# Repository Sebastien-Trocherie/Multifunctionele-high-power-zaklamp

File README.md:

# Multifunctionele-high-power-zaklamp

Het doel van dit project is om een zaklamp te maken die ik in verschillende situaties kan gebruiken, 

De zaklamp moet dus zeker 200-300m ver schijnen, om dit bereik te realiseren heeft de lamp toch een lichtintensiteit van meer dan 1000 lumen nodig. De bedoeling is dan ook om een high power LED te vinden die deze lichtintensiteit kan leveren. Verder moet de zaklamp zeker niet altijd zo fel zijn dus zal deze via PWM dimbaar zijn. Als extra functionaliteit wil ik via Bluetooth een string sturen naar de microcontroller die deze zal omzetten in morse code.

Het project bestaat uit 3 hoofddelen.

1) De Li-Ion batterij lader.

2) De LED driver die de LED zal aandrijven.

3) De microcontroller die het PWM signaal zal genereren en de morse code zal genereren.

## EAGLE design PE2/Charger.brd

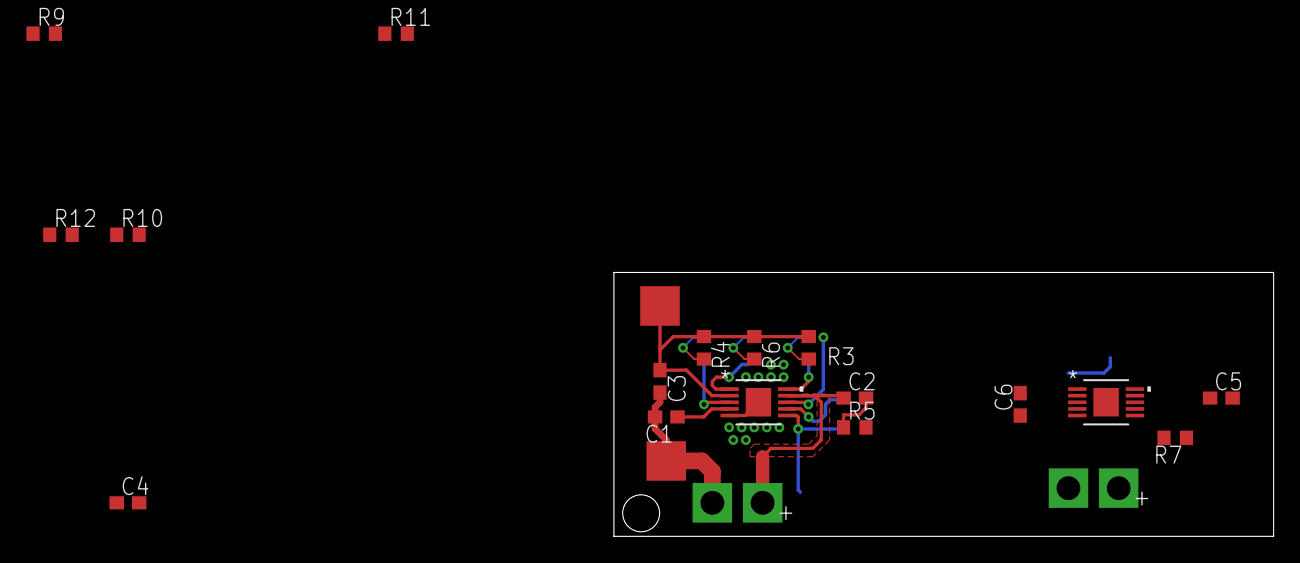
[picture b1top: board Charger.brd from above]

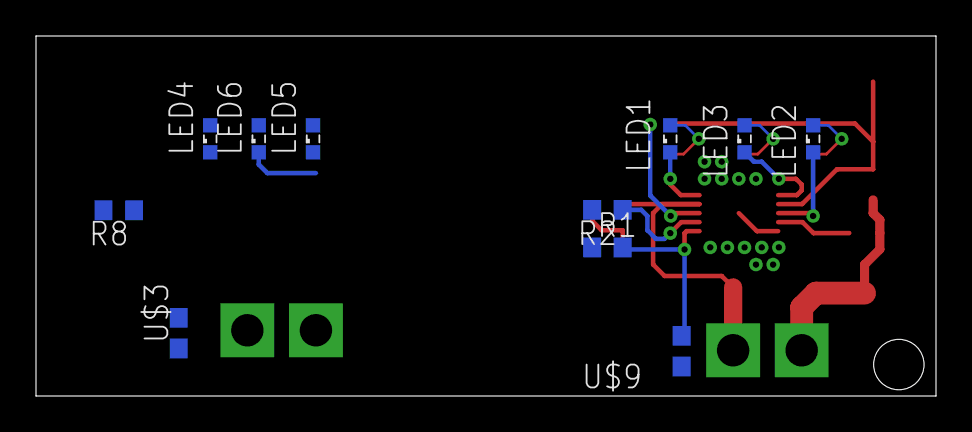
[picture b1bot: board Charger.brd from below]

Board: 2 copper layers, 50.0 x 20.0 mm, 32 parts (11 on the bottom side), 26 nets.

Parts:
BAT1: BATBAT; BAT2
BAT2: BAT; BAT2
C1, C4: 0.1uF; C0603
C2, C3, C5, C6: 4.7uF; C0603
LED1, LED2, LED3, LED4, LED5, LED6: SML0603
R1, R7: 475K; R0603
R2, R3, R4, R6, R8, R9, R10, R12: 1k; R0603
R5, R11: 1; R0603
U$1, U$2: LCT1733; MSOP-10_MSE
U$3, U$9: NTC; C0603
U$4, U$5: CONNECTOR; VCC

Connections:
GND: BAT1.P$2, BAT2.P$2, C1.2, C3.2, C4.2, R2.2, R5.2, R8.2, R11.2, U$1.5, U$1.11, U$2.5, U$2.11, U$3.2, U$5.P$1, U$9.2
unnamed: C3.1, R3.1, R4.1, R6.1, U$1.2, U$4.P$1
unnamed: R2.1, U$1.7
unnamed: LED1.C, U$1.10
unnamed: LED1.A, R3.2
unnamed: LED2.A, R4.2
unnamed: LED2.C, U$1.3
unnamed: BAT1.P$1, C2.1, U$1.9
unnamed: C2.2, R5.1
unnamed: C1.1, U$1.4
unnamed: LED3.A, R6.2
unnamed: LED3.C, U$1.1
unnamed: R1.2, U$1.6, U$9.1
unnamed: C6.1, R7.1, R9.1, R10.1, R12.1, U$2.2, U$2.8
unnamed: LED4.C, U$2.10
unnamed: LED4.A, R9.2
unnamed: LED5.A, R10.2
unnamed: LED5.C, U$2.3
unnamed: BAT2.P$1, C5.1, U$2.9
unnamed: R8.1, U$2.7
unnamed: C5.2, R11.1
unnamed: C4.1, U$2.4
unnamed: LED6.A, R12.2
unnamed: LED6.C, U$2.1
unnamed: R7.2, U$2.6, U$3.1
S$1: R1.1, U$1.8

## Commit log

2021-05-10 Program
2021-05-10 Initial controller code
    Quick test to see if the button and LED works
2021-05-10 PWM + Interrupt
    Hardware PWM TIM2 channel 1 @240HZ.
    And the mplementation of the button interrupt.
2021-05-10 Morse code
    Implementation of morse code in the seperate morse.c and h files.
2021-05-10 Full power mode
    2 short clicks to go into turbo mode.
2021-05-11 UART implementation
    Implementation of UART + cleaning up the code
2021-05-26 Update programs
